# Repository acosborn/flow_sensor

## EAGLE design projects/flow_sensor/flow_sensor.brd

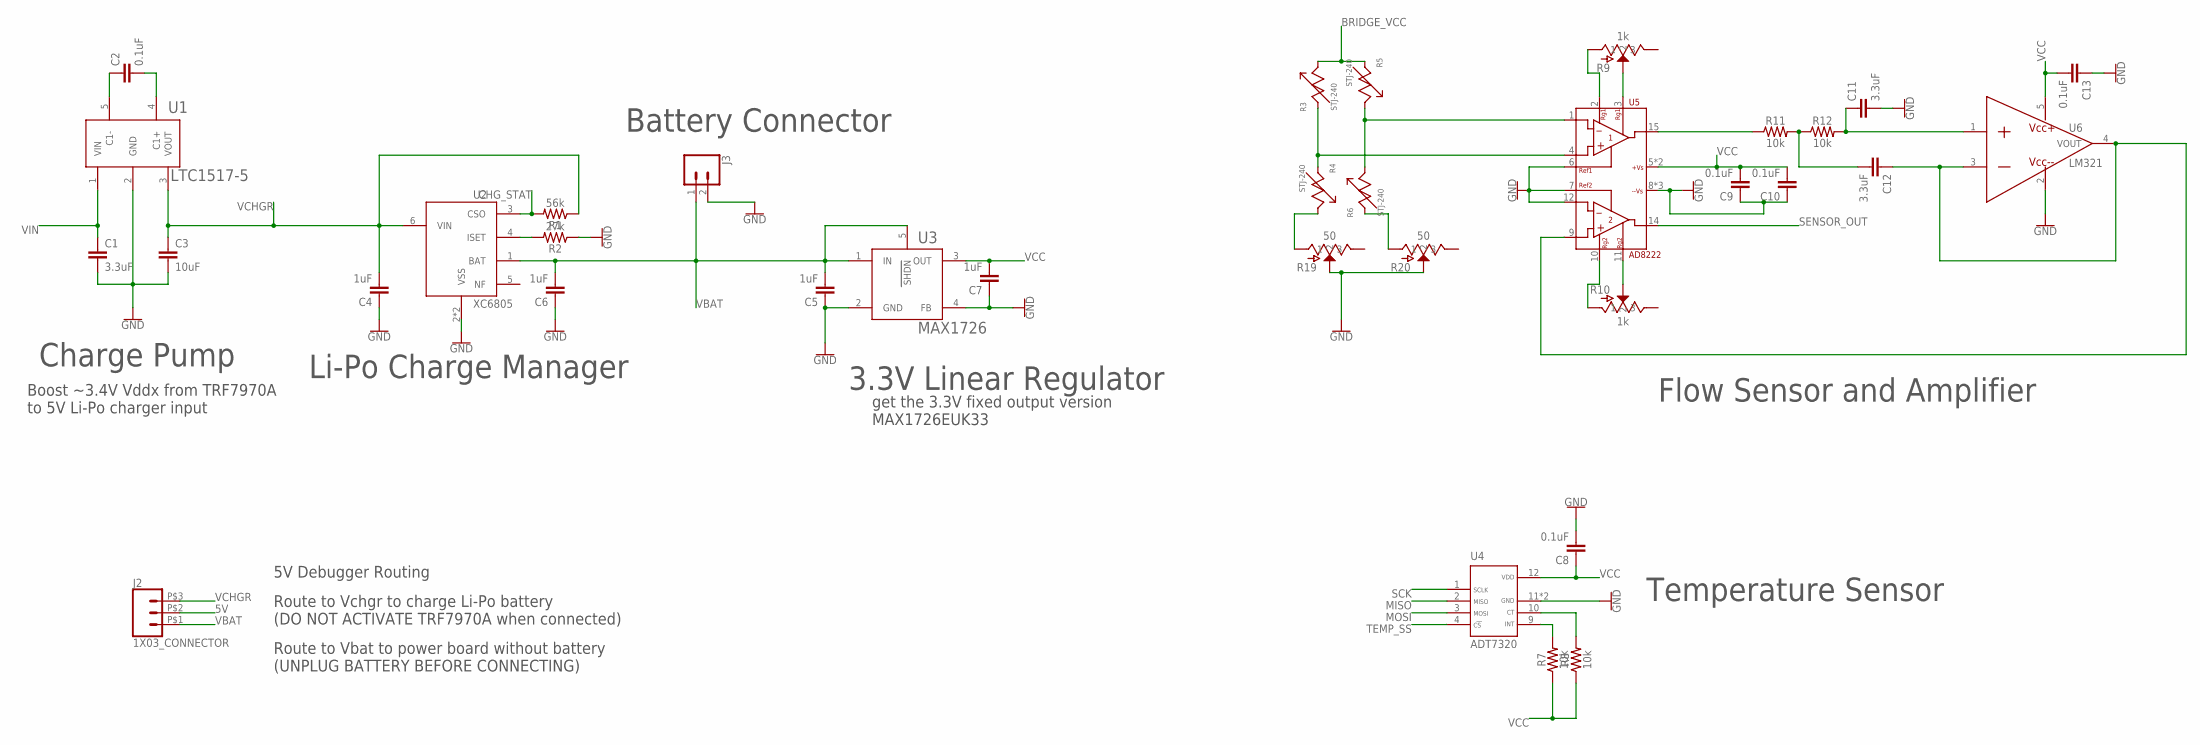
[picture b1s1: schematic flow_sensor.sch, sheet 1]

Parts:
C1, C11, C12: 3.3uF; 0603
C2, C8, C9, C10, C13: 0.1uF; 0603
C3: 10uF; 0603
C4, C5, C6, C7: 1uF; 0603
J2: 1X03_CONNECTOR; 1X03_SMD_HEADER
J3: CONN_021X02_NO_SILK; 1X02_NO_SILK
R1: 56k; 0603
R2: 27k; 0603
R3, R4, R5, R6: STJ-240; SOIC-8-NOCREAM
R7, R8, R11, R12: 10k; 0603
R9, R10: 1k; ST-32ETA
R19, R20: 50; ST-32ETA
U1: LTC1517-5; SOT-23-5
U2: XC6805; DFN6-1.8X2.0
U3: MAX1726; SOT-23-5
U4: ADT7320; QFN16-4X4
U5: AD8222; QFN16-4X4
U6: LM321; SOT-23-5

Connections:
5V: J2.P$2 (2); also elsewhere on the board
BRIDGE_VCC: R3.8, R5.1; also elsewhere on the board
CHG_STAT: R1.2, U2.3 (CSO); also elsewhere on the board
GND: C1.2, C3.2, C4.1, C5.1, C6.1, C7.1, C8.2, C9.1, C10.1, C11.2, C13.1, J3.2, R2.1, R19.2, R20.2, U1.2 (GND), U2.2 (VSS), U2.PAD (VSS), U3.2 (GND), U3.4 (FB), U4.11 (GND), U4.EXP (GND), U5.6 (REF1), U5.7 (REF2), U5.8 (-VS), U5.12 (-IN2), U5.13 (-VS), U5.EXP (-VS), U6.2 (VCC-); also elsewhere on the board
MISO: U4.2 (MISO); also elsewhere on the board
MOSI: U4.3 (MOSI); also elsewhere on the board
unnamed: C2.1, U1.5 (C1-)
unnamed: C2.2, U1.4 (C1+)
unnamed: R4.8, R19.1
unnamed: R7.2, U4.9 (INT)
unnamed: R6.1, R20.1
unnamed: R10.1, U5.10 (RG2)
unnamed: R3.1, R4.1, U5.4 (+IN1)
unnamed: C11.1, R12.2, U6.1 (IN+)
unnamed: C12.1, U5.9 (+IN2), U6.3 (IN-), U6.4 (VOUT)
unnamed: R9.1, U5.2 (RG1)
unnamed: R10.2, U5.11 (RG2')
unnamed: R8.2, U4.10 (CT)
unnamed: R9.2, U5.3 (RG1')
unnamed: R5.8, R6.8, U5.1 (-IN1)
unnamed: C12.2, R11.2, R12.1
unnamed: R2.2, U2.4 (ISET)
unnamed: R11.1, U5.15 (OUT1)
SCK: U4.1 (SCLK); also elsewhere on the board
SENSOR_OUT: U5.14 (OUT2); also elsewhere on the board
TEMP_SS: U4.4 (CS); also elsewhere on the board
VBAT: C5.2, C6.2, J2.P$1 (1), J3.1, U2.1 (BAT), U3.1 (IN), U3.5 (SHDN); also elsewhere on the board
VCC: C7.2, C8.1, C9.2, C10.2, C13.2, R7.1, R8.1, U3.3 (OUT), U4.12 (VDD), U5.5 (+VS), U5.16 (+VS), U6.5 (VCC+); also elsewhere on the board
VCHGR: C3.1, C4.2, J2.P$3 (3), R1.1, U1.3 (VOUT), U2.6 (VIN)
VIN: C1.1, U1.1 (VIN); also elsewhere on the board

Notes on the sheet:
get the 3.3V fixed output version MAX1726EUK33
Battery Connector
3.3V Linear Regulator
Li-Po Charge Manager
5V Debugger Routing
Route to Vchgr to charge Li-Po battery (DO NOT ACTIVATE TRF7970A when connected)
Route to Vbat to power board without battery (UNPLUG BATTERY BEFORE CONNECTING)
Temperature Sensor
Flow Sensor and Amplifier
Charge Pump
Boost ~3.4V Vddx from TRF7970A to 5V Li-Po charger input

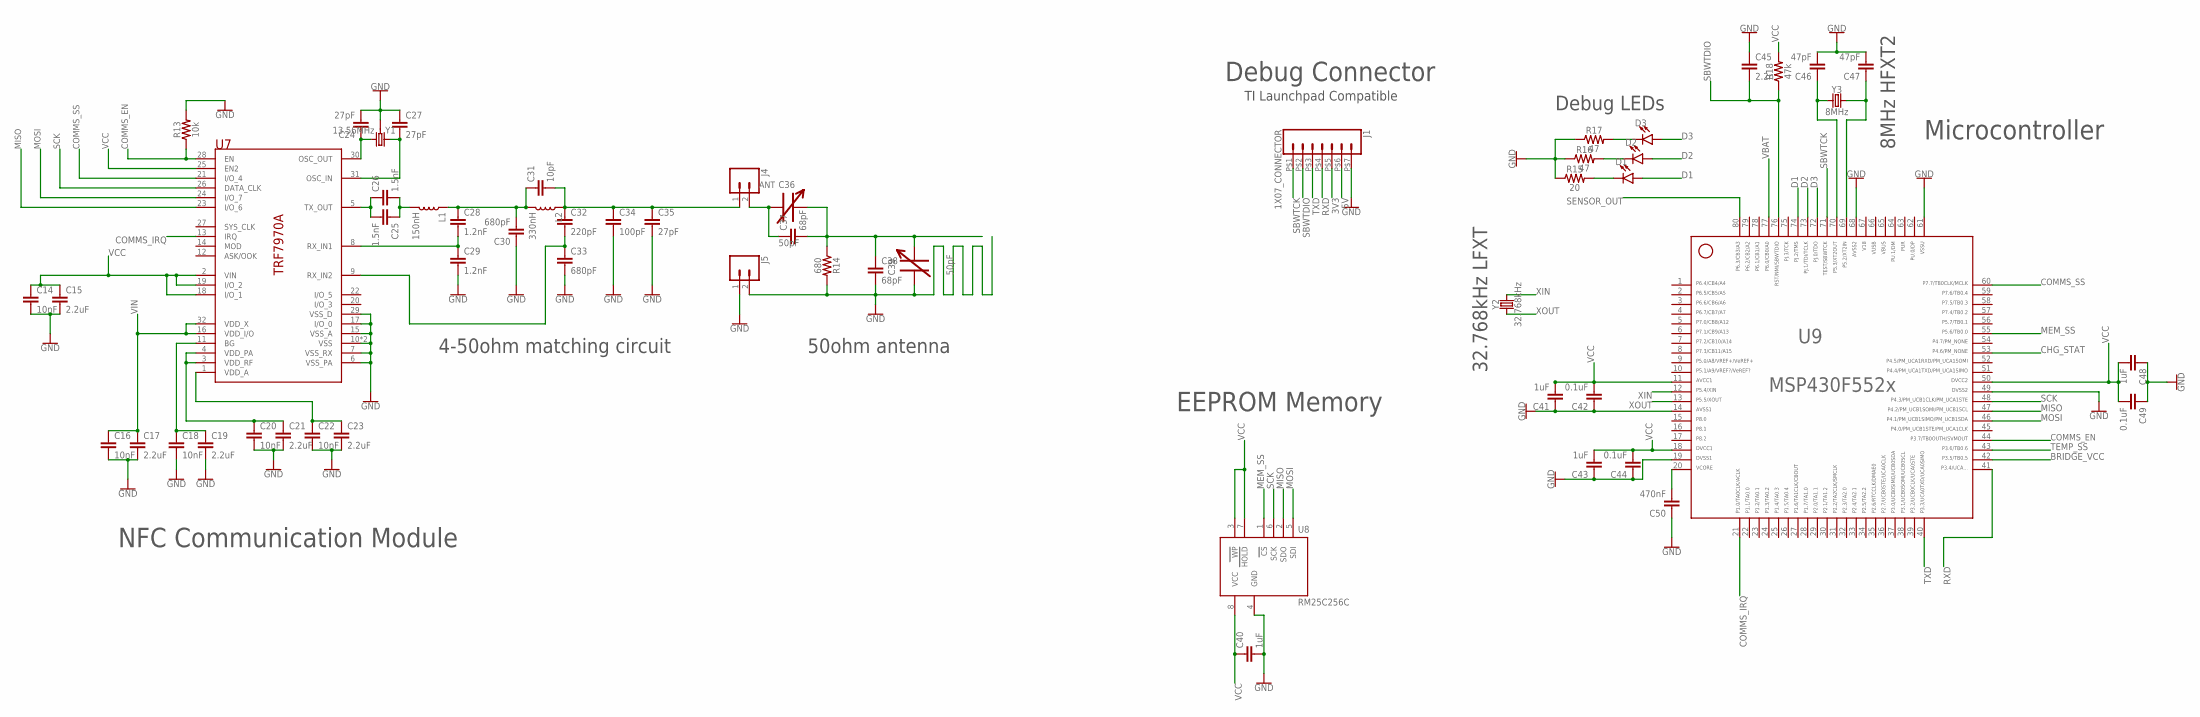
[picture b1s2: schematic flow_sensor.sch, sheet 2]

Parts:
C14, C16, C18, C20, C22: 10nF; 0603
C15, C17, C19, C21, C23: 2.2uF; 0603
C24, C27, C35: 27pF; 0603
C25, C26: 1.5nF; 0603
C28, C29: 1.2nF; 0603
C30, C33: 680pF; 0603
C31: 10pF; 0603
C32: 220pF; 0603
C34: 100pF; 0603
C36, C39: 50pF; TZY2_TRIM_CAP
C37, C38: 68pF; C2.5-2
C40, C41, C43, C48: 1uF; 0603
C42, C44, C49: 0.1uF; 0603
C45: 2.2n; 0603
C46, C47: 47pF; 0603
C50: 470nF; 0603
D1, D2, D3: LED0603; LED-0603
J1: 1X07_CONNECTOR; 1X07_SMD_HEADER
J4, J5: CONN_02; 1X02
L1: 150nH; 0603
L2: 330nH; 0603
R13: 10k; 0603
R14: 680; 0603
R15: 20; 0603
R16, R17: 47; 0603
R18: 47k; 0603
U7: TRF7970A; QFN-32
U8: RM25C256C; DFN8-2X3
U9: F552X---PN80; PN80
Y1: 13.56MHz; CRYSTAL-SMD-3.2X2.5MM
Y2: 32.768kHz; CRYSTAL-3.2X1.5
Y3: 8MHz; CRYSTAL-3.2X2.5

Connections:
3V3: J1.P$5 (5)
5V: J1.P$6 (6); also elsewhere on the board
65: U9.65
66: U9.66
67: U9.67
ANT: C31.2, C32.1, C34.1, C35.1, J4.1, L2.1
BRIDGE_VCC: U9.42; also elsewhere on the board
CHG_STAT: U9.53; also elsewhere on the board
COMMS_EN: R13.1, U7.28 (EN), U9.44
COMMS_IRQ: U7.13 (IRQ), U9.21
COMMS_SS: U7.21 (I/O_4), U9.60
D1: D1.A, U9.74
D2: D2.A, U9.73
D3: D3.A, U9.72
GND: C14.2, C15.2, C16.2, C17.2, C18.2, C19.2, C20.2, C21.2, C22.2, C23.2, C24.2, C27.1, C29.2, C30.1, C33.2, C34.2, C35.2, C38.2, C39.P$1, C40.2, C41.1, C42.1, C43.1, C44.1, C45.1, C46.2, C47.2, C48.1, C49.1, C50.1, J1.P$7 (7), J5.1, J5.2, R13.2, R14.2, R15.1, R16.1, R17.1, U7.6 (VSS_PA), U7.7 (VSS_RX), U7.10 (VSS), U7.15 (VSS_A), U7.17 (I/O_0), U7.29 (VSS_D), U7.EP (VSS), U8.4 (GND), U9.14, U9.19, U9.49, U9.61, U9.68, Y1.2 (3), Y1.4 (3); also elsewhere on the board
MEM_SS: U8.1 (CS), U9.55
MISO: U7.23 (I/O_6), U8.2 (SDO), U9.47; also elsewhere on the board
MOSI: U7.24 (I/O_7), U8.5 (SDI), U9.46; also elsewhere on the board
unnamed: D2.C, R16.2
unnamed: C24.1, U7.30 (OSC_OUT), Y1.3 (2)
unnamed: C18.1, C19.1, U7.11 (BG)
unnamed: C20.1, C21.1, U7.3 (VDD_RF), U7.4 (VDD_PA)
unnamed: C27.2, U7.31 (OSC_IN), Y1.1
unnamed: C22.1, C23.1, U7.1 (VDD_A)
unnamed: C25.2, C26.1, U7.5 (TX_OUT)
unnamed: C28.1, C30.2, C31.1, L1.1, L2.2
unnamed: C28.2, C29.1, U7.8 (RX_IN1)
unnamed: C25.1, C26.2, L1.2
unnamed: C32.2, C33.1, U7.9 (RX_IN2)
unnamed: C36.P$2, C37.2, C38.1, C39.P$2, R14.1
unnamed: C36.P$1, C37.1, J4.2
unnamed: C47.1, U9.69, Y3.2
unnamed: C46.1, U9.70, Y3.1
unnamed: C50.2, U9.20
unnamed: D3.C, R17.2
unnamed: D1.C, R15.2
RXD: J1.P$4 (4), U9.41
SBWTCK: J1.P$1 (1), U9.71
SBWTDIO: C45.2, J1.P$2 (2), R18.1, U9.76
SCK: U7.26 (DATA_CLK), U8.6 (SCK), U9.48; also elsewhere on the board
SENSOR_OUT: U9.80; also elsewhere on the board
TEMP_SS: U9.43; also elsewhere on the board
TXD: J1.P$3 (3), U9.40
VBAT: U9.77; also elsewhere on the board
VCC: C14.1, C15.1, C40.1, C41.2, C42.2, C43.2, C44.2, C48.2, C49.2, R18.2, U7.2 (VIN), U7.18 (I/O_1), U7.19 (I/O_2), U7.25 (EN2), U8.3 (WP), U8.7 (HOLD), U8.8 (VCC), U9.11, U9.18, U9.50; also elsewhere on the board
VIN: C16.1, C17.1, U7.16 (VDD_I/O), U7.32 (VDD_X); also elsewhere on the board
XIN: U9.12, Y2.P$2 (2)
XOUT: U9.13, Y2.P$1 (1)

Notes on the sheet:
Debug Connector
TI Launchpad Compatible
EEPROM Memory
Debug LEDs
8MHz HFXT2
32.768kHz LFXT
Microcontroller
NFC Communication Module
4-50ohm matching circuit
50ohm antenna

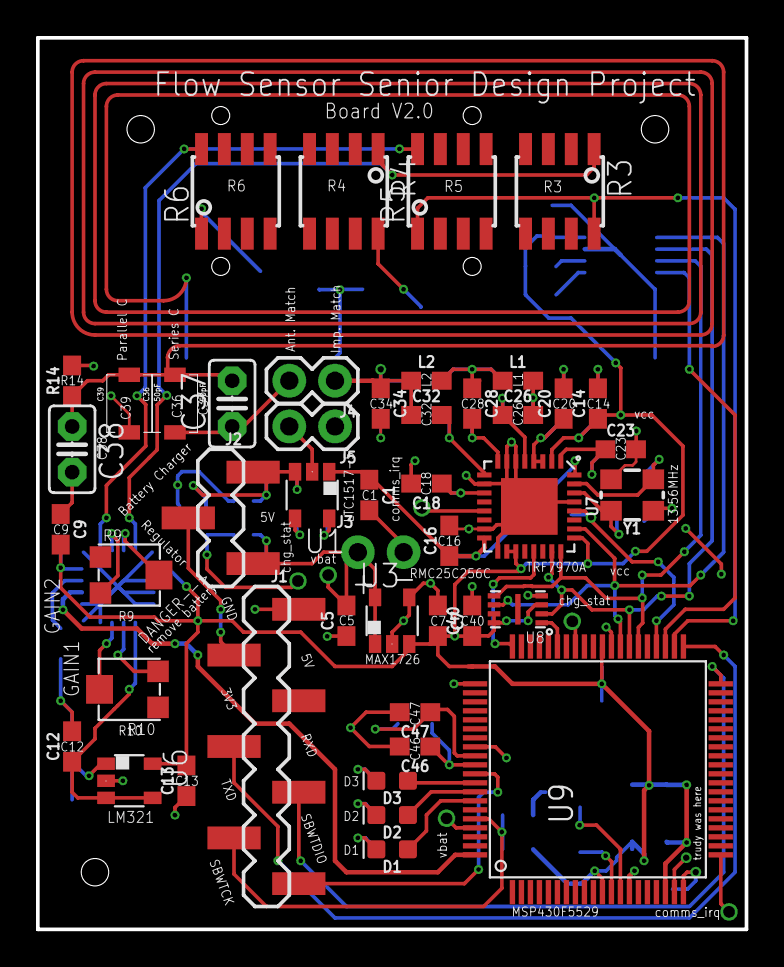
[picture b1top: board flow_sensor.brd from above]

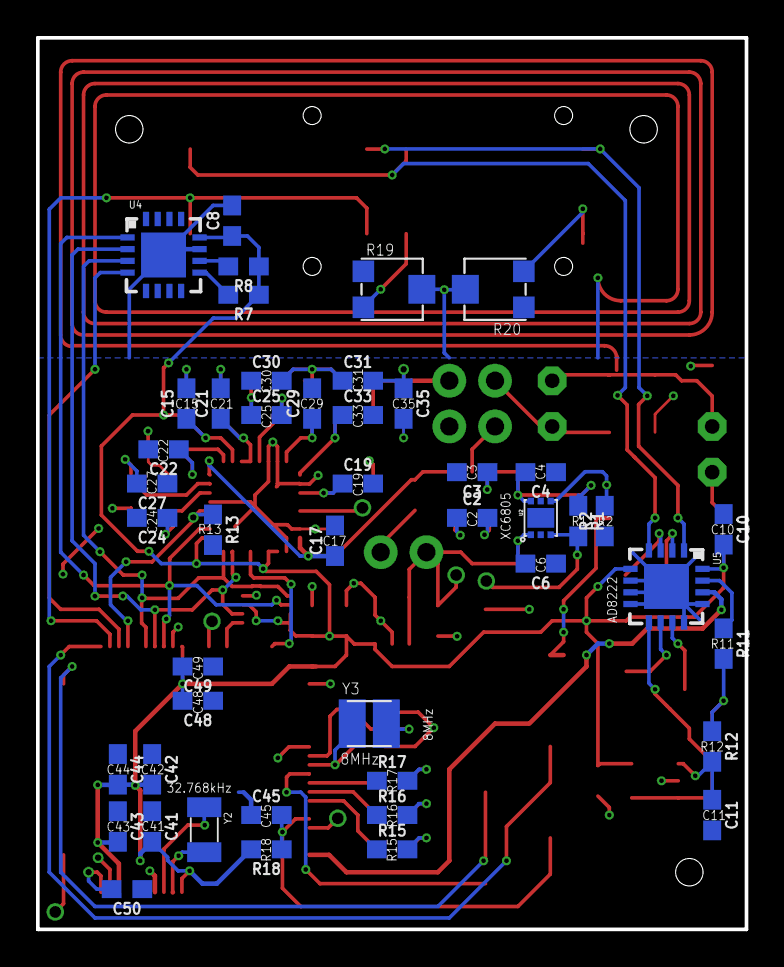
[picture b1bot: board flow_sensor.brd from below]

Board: 2 copper layers, 39.4 x 49.5 mm, 92 parts (46 on the bottom side), 62 nets.

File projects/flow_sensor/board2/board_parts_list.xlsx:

Part | Value | Device | Package | Description
R15 | 20Ω | RESISTOR | 0603
R16 | 47Ω | RESISTOR | 0603
R17 | 47Ω | RESISTOR | 0603
R19 | 50Ω | ST-32ETA | ST-32ETA
R20 | 50Ω | ST-32ETA | ST-32ETA
R14 | 680Ω | RESISTOR | 0603
C2 | 0.1uF | CAPACITOR_NONPOLARIZED | 0603
C8 | 0.1uF | CAPACITOR_NONPOLARIZED | 0603
C9 | 0.1uF | CAPACITOR_NONPOLARIZED | 0603
C10 | 0.1uF | CAPACITOR_NONPOLARIZED | 0603
C13 | 0.1uF | CAPACITOR_NONPOLARIZED | 0603
C42 | 0.1uF | CAPACITOR_NONPOLARIZED | 0603
C44 | 0.1uF | CAPACITOR_NONPOLARIZED | 0603
C49 | 0.1uF | CAPACITOR_NONPOLARIZED | 0603
C28 | 1.2nF | CAPACITOR_NONPOLARIZED | 0603
C29 | 1.2nF | CAPACITOR_NONPOLARIZED | 0603
C25 | 1.5nF | CAPACITOR_NONPOLARIZED | 0603
C26 | 1.5nF | CAPACITOR_NONPOLARIZED | 0603
C34 | 100pF | CAPACITOR_NONPOLARIZED | 0603
R7 | 10kΩ | RESISTOR | 0603
R8 | 10kΩ | RESISTOR | 0603
R11 | 10kΩ | RESISTOR | 0603
R12 | 10kΩ | RESISTOR | 0603
R13 | 10kΩ | RESISTOR | 0603
C14 | 10nF | CAPACITOR_NONPOLARIZED | 0603
C16 | 10nF | CAPACITOR_NONPOLARIZED | 0603
C18 | 10nF | CAPACITOR_NONPOLARIZED | 0603
C20 | 10nF | CAPACITOR_NONPOLARIZED | 0603
C22 | 10nF | CAPACITOR_NONPOLARIZED | 0603
C31 | 10pF | CAPACITOR_NONPOLARIZED | 0603
C3 | 10uF | CAPACITOR_NONPOLARIZED | 0603
Y1 | 13.56MHz | CRYSTAL-GROUNDEDSMD-3.2X2.5 | CRYSTAL-SMD-3.2X2.5MM | Crystals w/ Ground Pin (Generic)
L1 | 150nH | INDUCTOR | 0603
R9 | 1kΩ | ST-32ETA | ST-32ETA
R10 | 1kΩ | ST-32ETA | ST-32ETA
C4 | 1uF | CAPACITOR_NONPOLARIZED | 0603
C5 | 1uF | CAPACITOR_NONPOLARIZED | 0603
C6 | 1uF | CAPACITOR_NONPOLARIZED | 0603
C7 | 1uF | CAPACITOR_NONPOLARIZED | 0603
C40 | 1uF | CAPACITOR_NONPOLARIZED | 0603
C41 | 1uF | CAPACITOR_NONPOLARIZED | 0603
C43 | 1uF | CAPACITOR_NONPOLARIZED | 0603
C48 | 1uF | CAPACITOR_NONPOLARIZED | 0603
J2 | 1X03_CONNECTOR | 1X03_CONNECTOR | 1X03_SMD_HEADER
J1 | 1X07_CONNECTOR | 1X07_CONNECTOR | 1X07_SMD_HEADER
C45 | 2.2n | CAPACITOR_NONPOLARIZED | 0603
C15 | 2.2uF | CAPACITOR_NONPOLARIZED | 0603
C17 | 2.2uF | CAPACITOR_NONPOLARIZED | 0603
C19 | 2.2uF | CAPACITOR_NONPOLARIZED | 0603
C21 | 2.2uF | CAPACITOR_NONPOLARIZED | 0603
C23 | 2.2uF | CAPACITOR_NONPOLARIZED | 0603
C32 | 220pF | CAPACITOR_NONPOLARIZED | 0603
R2 | 27kΩ | RESISTOR | 0603
C24 | 27pF | CAPACITOR_NONPOLARIZED | 0603
C27 | 27pF | CAPACITOR_NONPOLARIZED | 0603
C35 | 27pF | CAPACITOR_NONPOLARIZED | 0603
C1 | 3.3uF | CAPACITOR_NONPOLARIZED | 0603
C11 | 3.3uF | CAPACITOR_NONPOLARIZED | 0603
C12 | 3.3uF | CAPACITOR_NONPOLARIZED | 0603
Y2 | 32.768kHz | CRYSTAL-3.2X1.5 | CRYSTAL-3.2X1.5
L2 | 330nH | INDUCTOR | 0603
C50 | 470nF | CAPACITOR_NONPOLARIZED | 0603
R18 | 47kΩ | RESISTOR | 0603
C46 | 47pF | CAPACITOR_NONPOLARIZED | 0603
C47 | 47pF | CAPACITOR_NONPOLARIZED | 0603
C36 | 50pF | TZY2_TRIM_CAP | TZY2_TRIM_CAP
C39 | 50pF | TZY2_TRIM_CAP | TZY2_TRIM_CAP
R1 | 56kΩ | RESISTOR | 0603
C30 | 680pF | CAPACITOR_NONPOLARIZED | 0603
C33 | 680pF | CAPACITOR_NONPOLARIZED | 0603
C37 | 68pF | C2.5/2 | C2.5-2 | CAPACITOR
C38 | 68pF | C2.5/2 | C2.5-2 | CAPACITOR
Y3 | 8MHz | CRYSTAL-3.2X2.5 | CRYSTAL-3.2X2.5
U5 | AD8222 | AD8222 | QFN16-4X4 | Precision
U4 | ADT7320 | ADT7320 | QFN16-4X4
U9 | F552X---PN80 | F552X---PN80 | PN80 | ***MSP430F552X***PN80
U6 | LM321 | LM321 | SOT-23-5 | Low-power
U1 | LTC1517-5 | LTC1517-5 | SOT-23-5 | Micropower
U3 | MAX1726 | MAX1726 | SOT-23-5
U8 | RM25C256C | RM25C256C | DFN8-2X3
R3 | STJ-240 | STJ-240 | SOIC-8-NOCREAM
R4 | STJ-240 | STJ-240 | SOIC-8-NOCREAM
R5 | STJ-240 | STJ-240 | SOIC-8-NOCREAM
R6 | STJ-240 | STJ-240 | SOIC-8-NOCREAM
U7 | TRF7970A | TRF7970A | QFN-32 | Multi-Protocol Fully Integrated 13.56-MHz NFC / RFID Transceiver IC
U2 | XC6805 | XC6805 | DFN6-1.8X2.0 | Single-Cell Li-ion/Li-polymer Linear Charger IC - Vin:4.5-6V - Iq:100uA - Icc: 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
D1 |  | LED0603 | LED-0603 | LED (Generic)
D2 |  | LED0603 | LED-0603 | LED (Generic)
D3 |  | LED0603 | LED-0603 | LED (Generic)
J3 |  | CONN_021X02_NO_SILK | 1X02_NO_SILK | Multi connection point. Often used as Generic Header-pin footprint for 0.1 inch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
J4 |  | CONN_02 | 1X02 | Multi connection point. Often used as Generic Header-pin footprint for 0.1 inch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
J5 |  | CONN_02 | 1X02 | Multi connection point. Often used as Generic Header-pin footprint for 0.1 inch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

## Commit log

2017-12-21 Repository Created
2017-12-21 Added library description (not important)
2017-12-21 Adjusted AD8222 schematic part
2018-01-01 AD8222 modified in library and connected in schematic
2018-01-01 Added LM8209 to library, finished sensor schematic
2018-01-04 Completed MSP430FR5994 part in library
2018-01-05 fixed BAS4002A pinout, added decoupling capacitors to uC
2018-01-08 Added Spi-Bi-Wire to uC, added SPI connections between uC/NFC
2018-01-10 Fixed BAS4002A part again
2018-01-12 Added QFN20-3.5mmx4.5mm package to library
2018-01-13 Completed BQ51013a library part
2018-01-24 Added INA826 instrumentation amplifier and DFN8-3x3 package
2018-01-24 Added LM321 OpAmp to library
2018-01-24 Added MAX4634 Mux to library
2018-01-24 Added AD8295 amp part to library
2018-01-24 Modified sensor: Added mux, reduced op-amps
2018-01-24 Adjusted LFCSP16-NP package document layer
2018-01-24 Work up to 1/24/18
2018-01-24 Resubmitting work for 1/24/18
2018-01-24 Changed sensor schematic to have 1 wheatstone bridge with 4 sensors
2018-01-27 Modified power supply to run off of NFC chip supply
2018-03-08 Board created, general save dump
2018-03-09 Second data dump. Board Layout Complete
2018-03-09 forgot to add board back to tracking
2018-03-09 Touched up board V1.0, added labels
2018-03-09 Finalized Board Size, touched up labels
2018-03-13 gerbers sent to fab v1.0
2018-03-13 starting v2.0
2018-03-13 forgot to add project epf file
2018-03-19 added stuff for board v2
2018-03-20 Added to to_do list
2018-04-03 Added MSP430F5229 to replace MSP430FR5994
2018-04-04 Added XC6805 battery charger to replace mcp73832
2018-04-04 Added MAX1726 linear regulator and replaced circuit-side boost converter
2018-04-04 Added LTC1517-5 charge pump to replace battery-site boost converter
2018-04-04 Added RM25C256C EEPROM for external data storage
2018-04-06 Beginning v2.0 routing
2018-04-09 Tentative board v2.0 complete
2018-04-11 Replaced 32k and 4M oscillator packages, added magnetic sensors, minor rewiring; board 2 almost ready for order
2018-04-13 Rewired SBW interface pins, LEDs, and Vbat bridge wire
2018-04-13 Board 2 complete
2018-04-18 Not important changes to board v2: WP and HOLD on EEPROM connected, shifted top 2 channel tiedown holes 1 mil right
2018-04-25 Added documentation to schematic
2018-05-01 Small adjustment to routes for memory module

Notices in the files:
parts and their libraries:
SparkFun-Connectors: Licensing: Creative Commons ShareAlike 4.0 International - https://creativecommons.org/licenses/by-sa/4.0
